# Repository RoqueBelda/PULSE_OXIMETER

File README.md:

# PULSE_OXIMETER-TFG-ROQUE-BELDA

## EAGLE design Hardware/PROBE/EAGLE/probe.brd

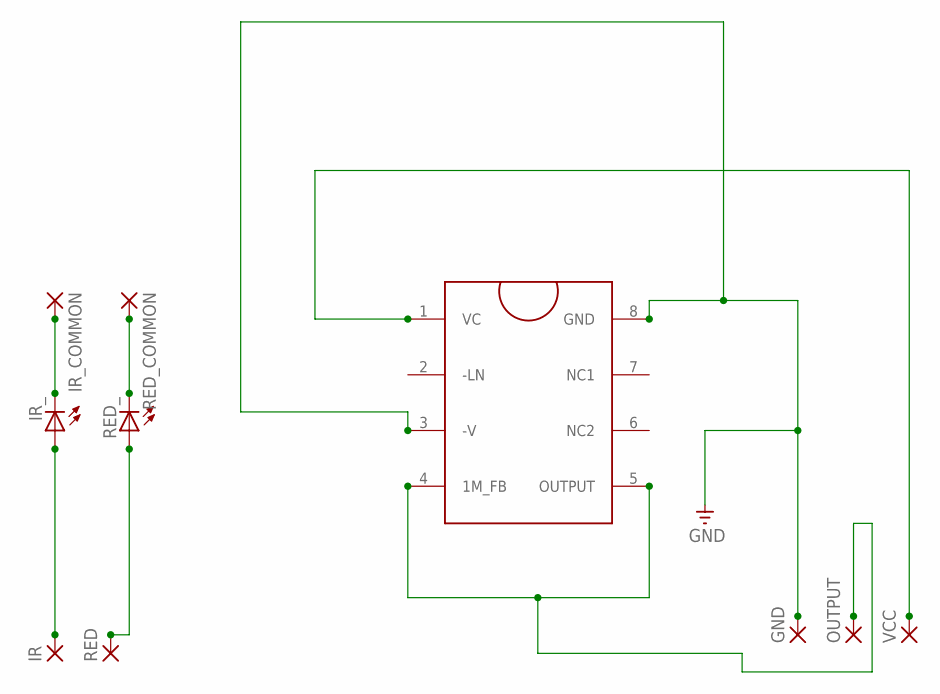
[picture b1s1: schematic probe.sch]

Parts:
GND: SMD2; SMD1,27-2,54
IR: SMD2; SMD1,27-2,54
IR_: LED_E; LED_1206
IR_COMMON: SMD2; SMD1,27-2,54
OUTPUT: SMD2; SMD1,27-2,54
RED: SMD2; SMD1,27-2,54
RED_: LED_E; LED_1206
RED_COMMON: SMD2; SMD1,27-2,54
U$1: OPT101; SO8
VCC: SMD2; SMD1,27-2,54

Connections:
GND: GND.1, U$1.3 (-V), U$1.8 (GND)
unnamed: U$1.1 (VC), VCC.1
unnamed: OUTPUT.1, U$1.4 (1M_FB), U$1.5 (OUTPUT)
unnamed: IR.1, IR_.A
unnamed: RED.1, RED_.A
unnamed: RED_.C, RED_COMMON.1
unnamed: IR_.C, IR_COMMON.1

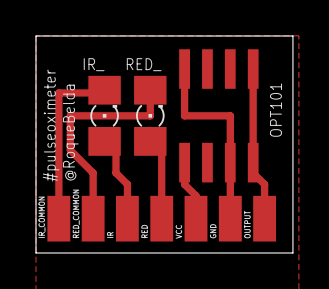
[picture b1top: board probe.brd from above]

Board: 2 copper layers, 14.3 x 12.1 mm, 10 parts (0 on the bottom side), 7 nets.

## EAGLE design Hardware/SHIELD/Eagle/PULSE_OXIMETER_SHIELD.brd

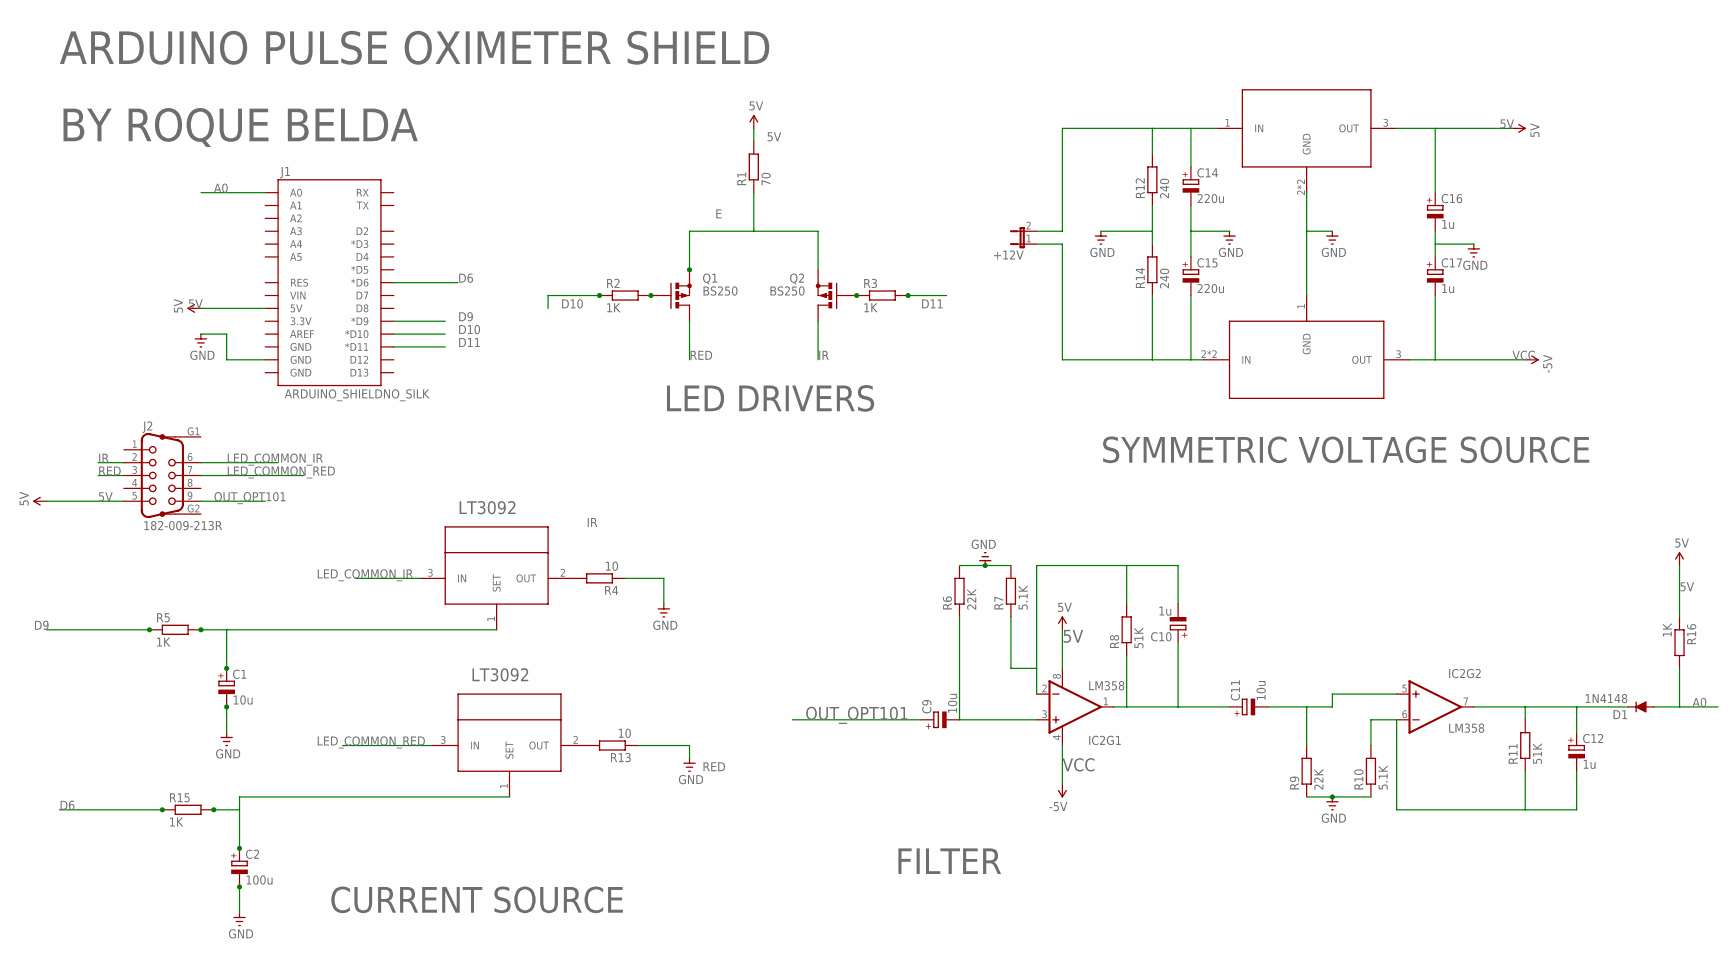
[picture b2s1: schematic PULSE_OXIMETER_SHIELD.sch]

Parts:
+12V: JP1E; JP1
C1, C9, C11: 10u; E2,5-6
C2: 100u; E2,5-6
C10, C12, C16, C17: 1u; E2,5-6
C14, C15: 220u; E3,5-8
D1: 1N4148; DO35-10
IC2: LM358; DIP08
J1: ARDUINO_SHIELDNO_SILK; DUEMILANOVE_VIAS
J2: 182-009-213R
Q1, Q2: BS250; SOT54E
R1: 70; 0204/5
R2, R3, R5, R15, R16: 1K; 0204/5
R4, R13: 10; 0204/5
R6, R9: 22K; 0204/5
R7, R10: 5.1K; 0204/5
R8, R11: 51K; 0204/5
R12, R14: 240; 0204/5
U$1, U$4: LT3092; SOT223
U$2: UA78M05; SOT223
U$3: UA79M05; TO263-3

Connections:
5V: C16.+, IC2.8 (V+), J1.5V, J2.5, R1.2, R16.1, U$2.3 (OUT)
A0: D1.A, J1.A0, R16.2
C10: C10.+, C11.+, IC2.1 (OUT), R8.1
D6: J1.D6 (*D6), R15.1
D9: J1.D9 (*D9), R5.1
D10: J1.D10 (*D10), R2.1
D11: J1.D11 (*D11), R3.2
E: Q1.S, Q2.S, R1.1
GND: C1.-, C2.-, C14.-, C15.+, J1.GND@1 (GND), R4.1, R6.2, R7.2, R9.1, R10.1, R13.1, U$2.2 (GND), U$2.4 (GND), U$3.1 (GND)
IR: J2.2, Q2.D
LED_COMMON_IR: J2.6, U$1.3 (IN)
LED_COMMON_RED: J2.7, U$4.3 (IN)
unnamed: Q1.G, R2.2
unnamed: Q2.G, R3.1
unnamed: R4.2, U$1.2 (OUT)
unnamed: C2.+, R15.2, U$4.1 (SET)
unnamed: C1.+, R5.2, U$1.1 (SET)
unnamed: C11.-, IC2.5 (+IN), R9.2
unnamed: R13.2, U$4.2 (OUT)
unnamed: C12.+, D1.C, IC2.7 (OUT), R11.2
unnamed: C16.-, C17.+
unnamed: +12V.2, C14.+, R12.2, U$2.1 (IN)
unnamed: R12.1, R14.2
unnamed: +12V.1, C15.-, R14.1, U$3.2 (IN), U$3.4 (IN)
unnamed: C10.-, IC2.2 (-IN), R7.1, R8.2
unnamed: C9.-, IC2.3 (+IN), R6.1
OUT_OPT101: C9.+, J2.9
R11: C12.-, IC2.6 (-IN), R10.2, R11.1
RED: J2.3, Q1.D
VCC: C17.-, IC2.4 (V-), U$3.3 (OUT)

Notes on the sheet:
SYMMETRIC VOLTAGE SOURCE
LED DRIVERS
CURRENT SOURCE
FILTER
RED
ARDUINO PULSE OXIMETER SHIELD
BY ROQUE BELDA

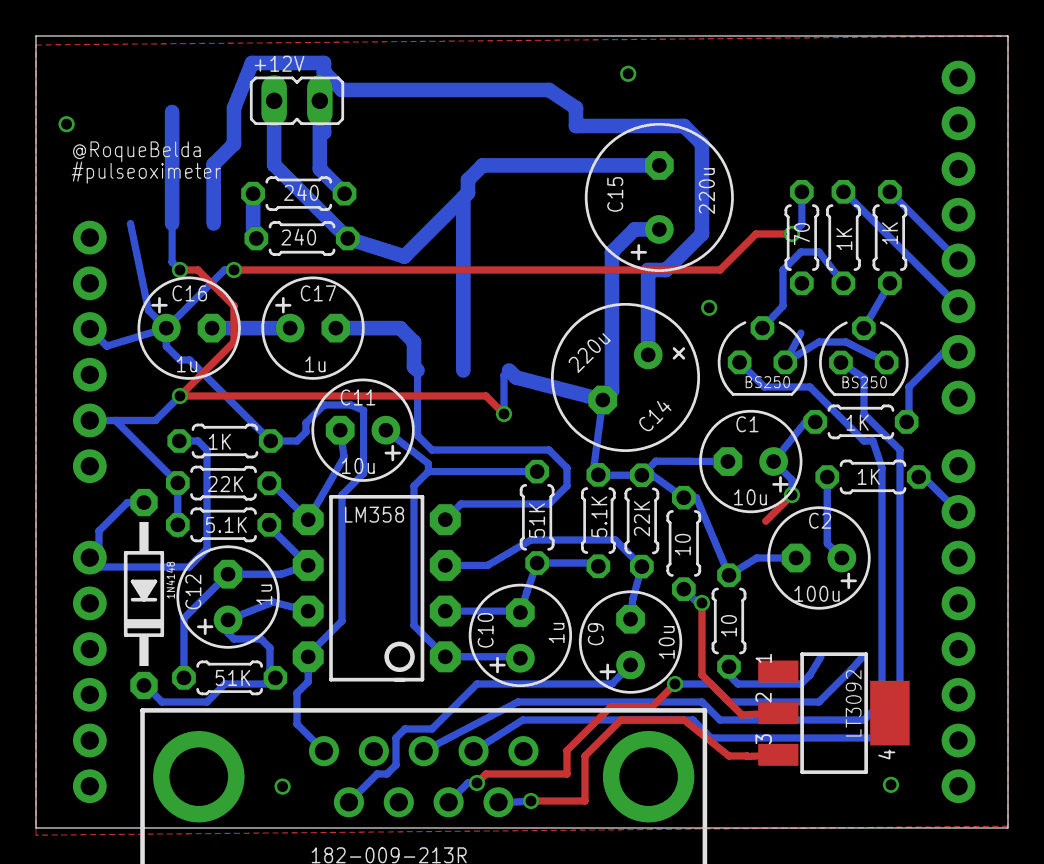
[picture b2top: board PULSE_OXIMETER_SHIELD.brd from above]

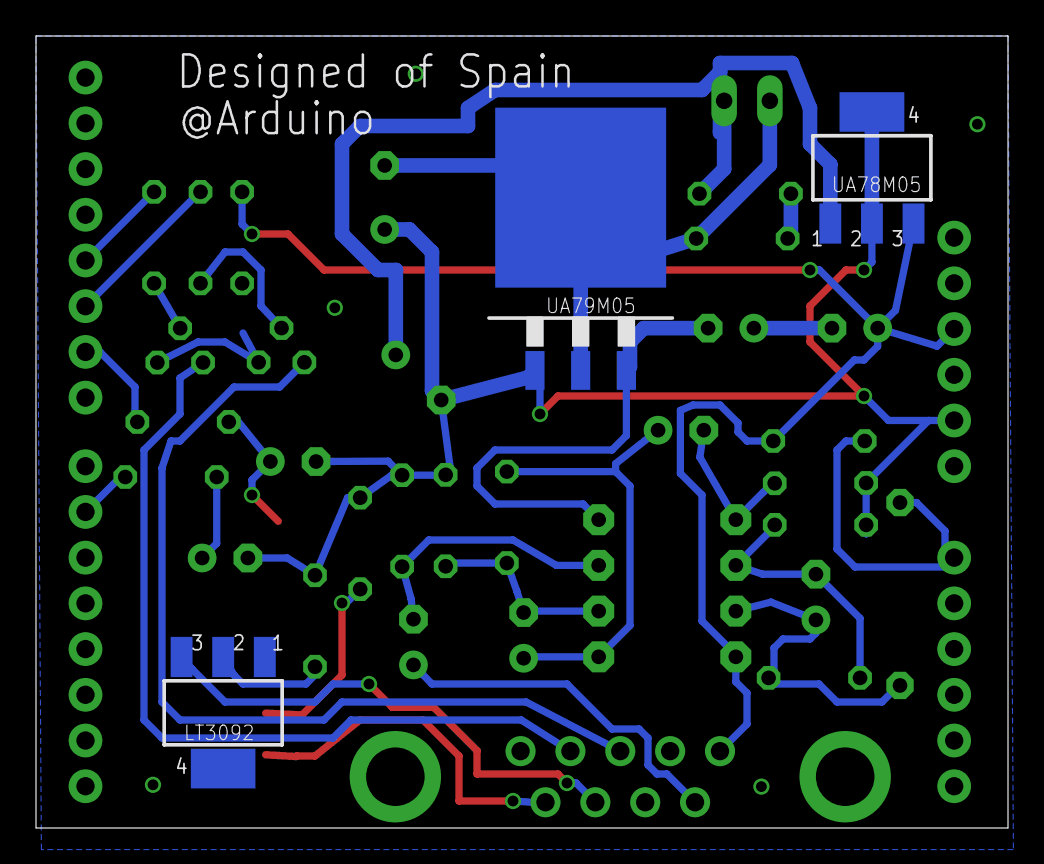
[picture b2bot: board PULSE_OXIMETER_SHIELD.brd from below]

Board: 2 copper layers, 54.0 x 44.0 mm, 37 parts (3 on the bottom side), 30 nets.

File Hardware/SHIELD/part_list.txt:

Partlist

Exported from PULSE_OXIMETER_SHIELD.sch at 03/10/2016 13:07

EAGLE Version 7.6.0 Copyright (c) 1988-2016 CadSoft

Assembly variant: 

Part     Value                 Device                Package          Library                 Sheet

+12V                           JP1E                  JP1              jumper                  1
C1       10u                   CPOL-EUE2.5-6         E2,5-6           resistor                1
C2       100u                  CPOL-EUE2.5-6         E2,5-6           resistor                1
C9       10u                   CPOL-EUE2.5-6         E2,5-6           resistor                1
C10      1u                    CPOL-EUE2.5-6         E2,5-6           resistor                1
C11      10u                   CPOL-EUE2.5-6         E2,5-6           resistor                1
C12      1u                    CPOL-EUE2.5-6         E2,5-6           resistor                1
C14      220u                  CPOL-EUE3.5-8         E3,5-8           resistor                1
C15      220u                  CPOL-EUE3.5-8         E3,5-8           resistor                1
C16      1u                    CPOL-EUE2.5-6         E2,5-6           resistor                1
C17      1u                    CPOL-EUE2.5-6         E2,5-6           resistor                1
D1       1N4148                1N4148                DO35-10          diode (2)               1
IC2      LM358                 LM358                 DIP08            SparkFun-AnalogIC       1
J1       ARDUINO_SHIELDNO_SILK ARDUINO_SHIELDNO_SILK DUEMILANOVE_VIAS SparkFun-Boards         1
J2       182-009-213R          182-009-213R          182-009-213R     con-subd (2)            1
Q1       BS250                 BS250                 SOT54E           transistor-small-signal 1
Q2       BS250                 BS250                 SOT54E           transistor-small-signal 1
R1       70                    R-EU_0204/5           0204/5           rcl                     1
R2       1K                    R-EU_0204/5           0204/5           rcl                     1
R3       1K                    R-EU_0204/5           0204/5           rcl                     1
R4       10                    R-EU_0204/5           0204/5           rcl                     1
R5       1K                    R-EU_0204/5           0204/5           rcl                     1
R6       22K                   R-EU_0204/5           0204/5           rcl                     1
R7       5.1K                  R-EU_0204/5           0204/5           rcl                     1
R8       51K                   R-EU_0204/5           0204/5           rcl                     1
R9       22K                   R-EU_0204/5           0204/5           rcl                     1
R10      5.1K                  R-EU_0204/5           0204/5           rcl                     1
R11      51K                   R-EU_0204/5           0204/5           rcl                     1
R12      240                   R-EU_0204/5           0204/5           rcl                     1
R13      10                    R-EU_0204/5           0204/5           rcl                     1
R14      240                   R-EU_0204/5           0204/5           rcl                     1
R15      1K                    R-EU_0204/5           0204/5           rcl                     1
R16      1K                    R-EU_0204/5           0204/5           rcl                     1
U$1      LT3092                LT3092                SOT223           transistor-npn          1
U$2      UA78M05               UA78M05               SOT223           transistor-npn          1
U$3      UA79M05               UA79M05               TO263-3          lm1084-adj-to263        1
U$4      LT3092                LT3092                SOT223           transistor-npn          1

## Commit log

2016-10-03 Pulse Oximeter

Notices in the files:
parts and their libraries:
SparkFun-AnalogIC: Licensing:Creative Commons ShareAlike 4.0 International - https://creativecommons.org/licenses/by-sa/4.0
